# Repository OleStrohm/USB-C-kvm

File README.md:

# USB C kvm
A USB C kvm used to switch one output connection between two input connections.

This allows one to connect a peripheral to the output and a computer to each
input, and then switch which computer it should be connected to with the press
of a button.

## Goals
These are the design goals I'm aiming for:

* Full speed USB C including PD.
* Cheap and robust implementation
* SMD, but solderable by hand.

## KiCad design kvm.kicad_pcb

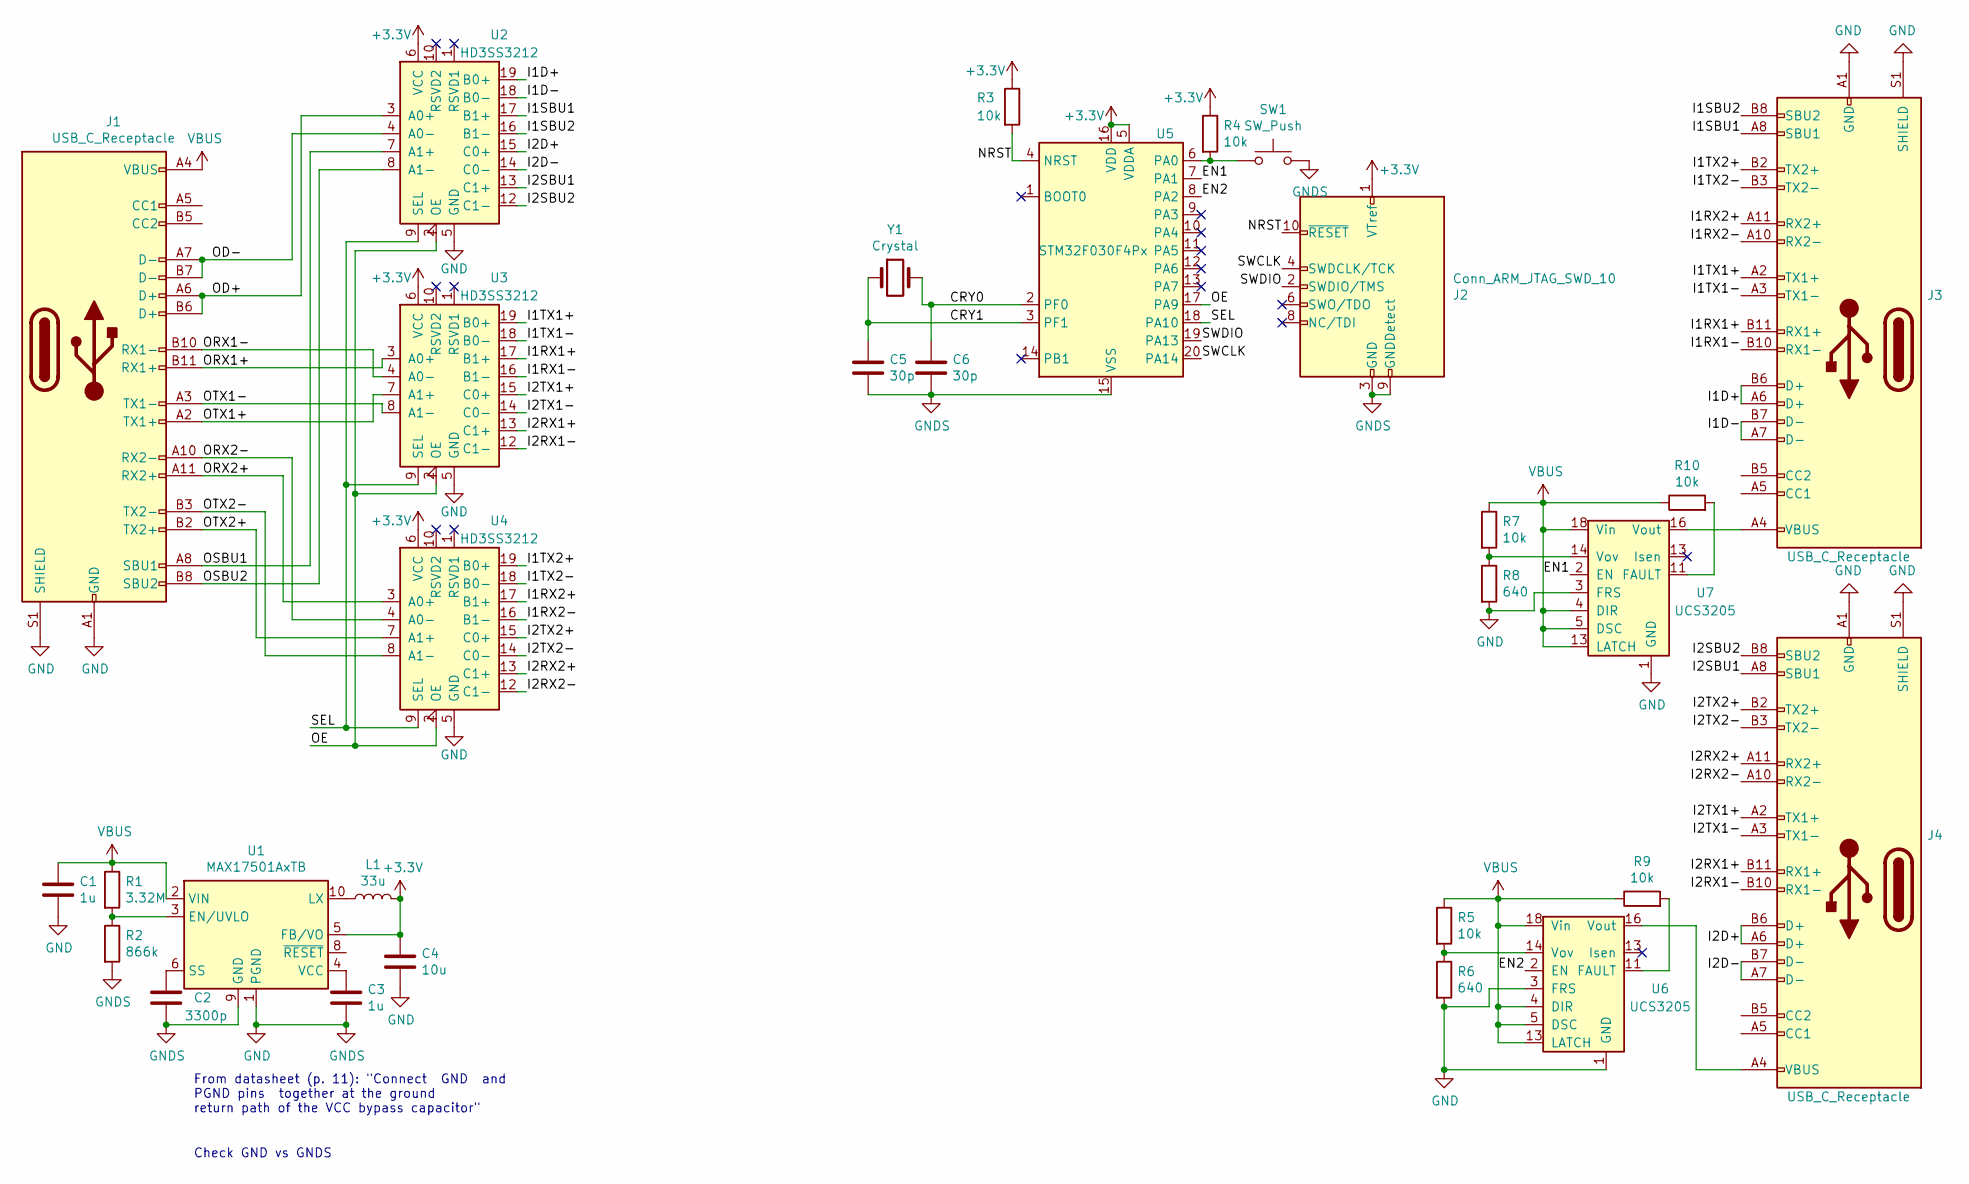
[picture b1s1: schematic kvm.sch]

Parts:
C1, C3: 1u; C_0805_2012Metric
C2: 3300p; C_0805_2012Metric
C4: 10u; C_1206_3216Metric
C5, C6: 30p; C_0805_2012Metric
J1, J3, J4: USB_C_Receptacle; USB_C_Receptacle_Amphenol_12401548E4-2A
J2: Conn_ARM_JTAG_SWD_10; PinHeader_2x05_P1.27mm_Vertical_SMD
L1: 33u; L_0805_2012Metric
R1: 3.32M; R_0805_2012Metric
R2: 866k; R_0805_2012Metric
R3, R4, R5, R7, R9, R10: 10k; R_0805_2012Metric
R6, R8: 640; R_0805_2012Metric
SW1: SW_Push; SW_SPST_B3S-1000
U1: MAX17501AxTB; TDFN-10-1EP_2x3mm_P0.5mm_EP0.9x2mm
U2, U3, U4: HD3SS3212; VQFN20RKS
U5: STM32F030F4Px; TSSOP-20_4.4x6.5mm_P0.65mm
U6, U7: UCS3205; VQFN19_3x3x0.9mm
Y1: Crystal; Crystal_HC49-4H_Vertical

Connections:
+3V3: C4.1, J2.1 (VTref), L1.2, R3.1, R4.1, U1.5 (FB/VO), U2.6 (VCC), U3.6 (VCC), U4.6 (VCC), U5.5 (VDDA), U5.16 (VDD)
/CRY0: C6.1, U5.2 (PF0), Y1.2
/CRY1: C5.1, U5.3 (PF1), Y1.1
/EN1: U5.7 (PA1), U7.2 (EN)
/EN2: U5.8 (PA2), U6.2 (EN)
/I1D+: J3.A6 (D+), J3.B6 (D+), U2.19 (B0+)
/I1D-: J3.A7 (D-), J3.B7 (D-), U2.18 (B0-)
/I1RX1+: J3.B11 (RX1+), U3.17 (B1+)
/I1RX1-: J3.B10 (RX1-), U3.16 (B1-)
/I1RX2+: J3.A11 (RX2+), U4.17 (B1+)
/I1RX2-: J3.A10 (RX2-), U4.16 (B1-)
/I1SBU1: J3.A8 (SBU1), U2.17 (B1+)
/I1SBU2: J3.B8 (SBU2), U2.16 (B1-)
/I1TX1+: J3.A2 (TX1+), U3.19 (B0+)
/I1TX1-: J3.A3 (TX1-), U3.18 (B0-)
/I1TX2+: J3.B2 (TX2+), U4.19 (B0+)
/I1TX2-: J3.B3 (TX2-), U4.18 (B0-)
/I2D+: J4.A6 (D+), J4.B6 (D+), U2.15 (C0+)
/I2D-: J4.A7 (D-), J4.B7 (D-), U2.14 (C0-)
/I2RX1+: J4.B11 (RX1+), U3.13 (C1+)
/I2RX1-: J4.B10 (RX1-), U3.12 (C1-)
/I2RX2+: J4.A11 (RX2+), U4.13 (C1+)
/I2RX2-: J4.A10 (RX2-), U4.12 (C1-)
/I2SBU1: J4.A8 (SBU1), U2.13 (C1+)
/I2SBU2: J4.B8 (SBU2), U2.12 (C1-)
/I2TX1+: J4.A2 (TX1+), U3.15 (C0+)
/I2TX1-: J4.A3 (TX1-), U3.14 (C0-)
/I2TX2+: J4.B2 (TX2+), U4.15 (C0+)
/I2TX2-: J4.B3 (TX2-), U4.14 (C0-)
/NRST: J2.10 (~RESET~), R3.2, U5.4 (NRST)
/OD+: J1.A6 (D+), J1.B6 (D+), U2.3 (A0+)
/OD-: J1.A7 (D-), J1.B7 (D-), U2.4 (A0-)
/OE: U2.2 (OE), U3.2 (OE), U4.2 (OE), U5.17 (PA9)
/ORX1+: J1.B11 (RX1+), U3.3 (A0+)
/ORX1-: J1.B10 (RX1-), U3.4 (A0-)
/ORX2+: J1.A11 (RX2+), U4.3 (A0+)
/ORX2-: J1.A10 (RX2-), U4.4 (A0-)
/OSBU1: J1.A8 (SBU1), U2.7 (A1+)
/OSBU2: J1.B8 (SBU2), U2.8 (A1-)
/OTX1+: J1.A2 (TX1+), U3.7 (A1+)
/OTX1-: J1.A3 (TX1-), U3.8 (A1-)
/OTX2+: J1.B2 (TX2+), U4.7 (A1+)
/OTX2-: J1.B3 (TX2-), U4.8 (A1-)
/SEL: U2.9 (SEL), U3.9 (SEL), U4.9 (SEL), U5.18 (PA10)
/SWCLK: J2.4 (SWDCLK/TCK), U5.20 (PA14)
/SWDIO: J2.2 (SWDIO/TMS), U5.19 (PA13)
GND: C1.2, C2.2, C3.2, C4.2, C5.2, C6.2, J1.A1 (GND), J1.A12 (GND), J1.B1 (GND), J1.B12 (GND), J1.S1 (SHIELD), J2.3 (GND), J2.5 (GND), J2.9 (GNDDetect), J3.A1 (GND), J3.A12 (GND), J3.B1 (GND), J3.B12 (GND), J3.S1 (SHIELD), J4.A1 (GND), J4.A12 (GND), J4.B1 (GND), J4.B12 (GND), J4.S1 (SHIELD), R2.2, R6.2, R8.2, SW1.2, U1.1 (PGND), U1.9 (GND), U1.11 (GND), U2.0 (GND), U2.5 (GND), U2.11 (GND), U2.20 (GND), U3.0 (GND), U3.5 (GND), U3.11 (GND), U3.20 (GND), U4.0 (GND), U4.5 (GND), U4.11 (GND), U4.20 (GND), U5.15 (VSS), U6.1 (GND), U6.3 (FRS), U6.15 (GND), U7.1 (GND), U7.3 (FRS), U7.15 (GND)
unnamed: C2.1, U1.6 (SS)
unnamed: C3.1, U1.4 (VCC)
unnamed: J3.A4 (VBUS), J3.A9 (VBUS), J3.B4 (VBUS), J3.B9 (VBUS), U7.16 (Vout), U7.17 (Vout), U7.21 (Vout)
unnamed: J4.A4 (VBUS), J4.A9 (VBUS), J4.B4 (VBUS), J4.B9 (VBUS), U6.16 (Vout), U6.17 (Vout), U6.21 (Vout)
unnamed: L1.1, U1.10 (LX)
unnamed: R1.2, R2.1, U1.3 (EN/UVLO)
unnamed: R4.2, SW1.1, U5.6 (PA0)
unnamed: R5.2, R6.1, U6.14 (Vov)
unnamed: R7.2, R8.1, U7.14 (Vov)
unnamed: R9.2, U6.11 (FAULT)
unnamed: R10.2, U7.11 (FAULT)
VBUS: C1.1, J1.A4 (VBUS), J1.A9 (VBUS), J1.B4 (VBUS), J1.B9 (VBUS), R1.1, R5.1, R7.1, R9.1, R10.1, U1.2 (VIN), U6.4 (DIR), U6.5 (DSC), U6.13 (Isen), U6.18 (Vin), U6.19 (Vin), U6.20 (Vin), U7.4 (DIR), U7.5 (DSC), U7.13 (Isen), U7.18 (Vin), U7.19 (Vin), U7.20 (Vin)

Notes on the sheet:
From datasheet (p. 11): "Connect GND and PGND pins together at the ground return path of the VCC bypass capacitor"
Check GND vs GNDS

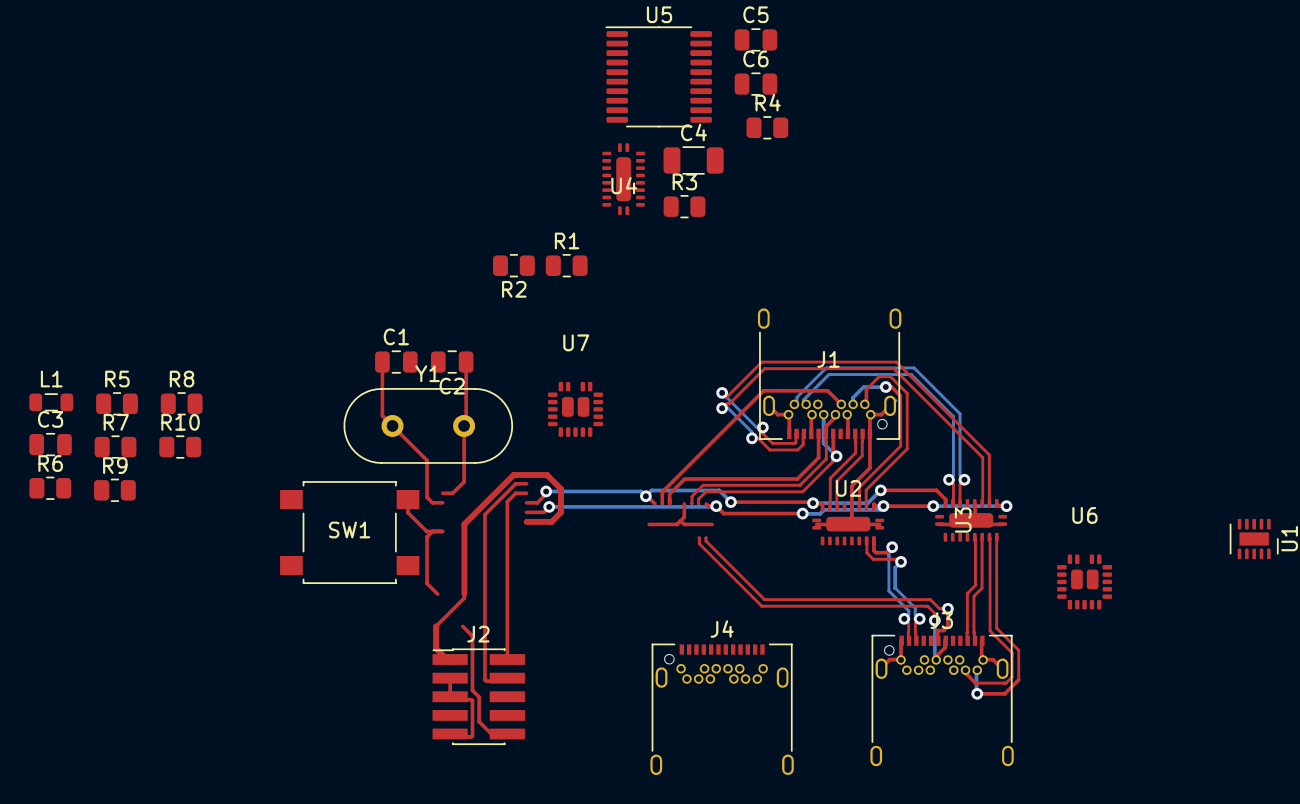
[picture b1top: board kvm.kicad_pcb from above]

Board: 4 copper layers, 30 parts (0 on the bottom side), 59 nets.

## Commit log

2021-05-31 Initial commit
    Almost got the data switching working. Power and control ciruit is
    unimplemented.
2021-05-31 Create LICENSE
2021-06-11 Added a micro controller and SWD header
2021-06-18 Added a power buffer on VBus
2021-06-22 finished PD switches and added 3.3V PSU
2021-06-23 Added PD, maybe finished v1!
2021-06-24 Fixed errors in component schematics and added decoupling caps
2021-10-11 Added separate power input for control circuit
2021-10-11 Added annotations
